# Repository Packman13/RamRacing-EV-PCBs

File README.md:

# RamRacing-EV-PCBs
Full schematic and PCB designs for RAM Racing’s Formula SAE Electric Vehicle. Includes tractive system active light, hard fault latch, precharge/discharge circuits, and the complete EV schematic. Provided for reference and educational purposes.

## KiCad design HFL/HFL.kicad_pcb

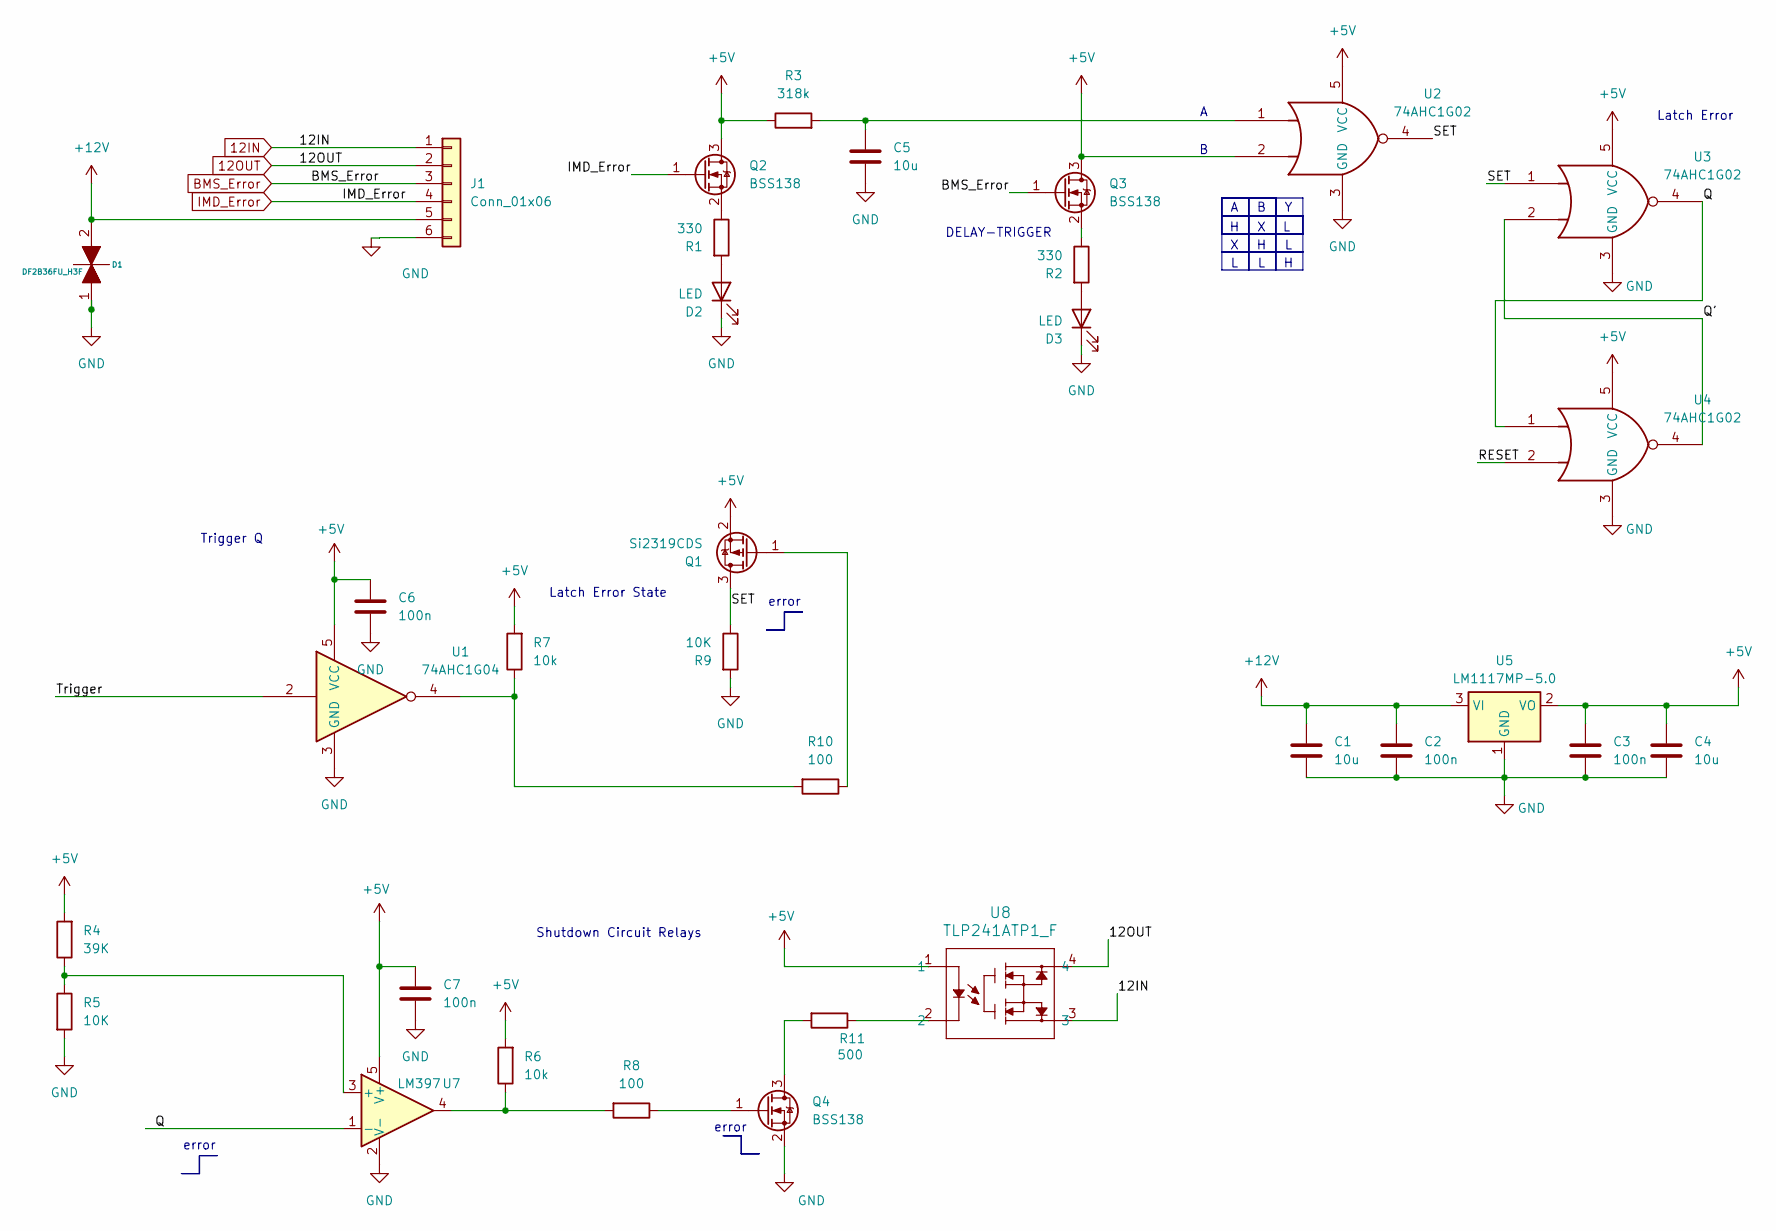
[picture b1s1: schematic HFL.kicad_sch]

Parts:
C1, C4, C5: 10u; C_0603_1608Metric_Pad1.08x0.95mm_HandSolder
C2, C3, C6, C7: 100n; C_0603_1608Metric_Pad1.08x0.95mm_HandSolder
D1: DF2B36FU_H3F; SOD-323 USC_TOS
D2, D3: LED; LED_0805_2012Metric
J1: Conn_01x06; TE_DT13-6P
Q1: Si2319CDS; SOT-23
Q2, Q3, Q4: BSS138; SOT-23
R1, R2: 330; R_0603_1608Metric
R3: 318k; R_0603_1608Metric
R4: 39K; R_0603_1608Metric
R5, R9: 10K; R_0603_1608Metric
R6, R7: 10k; R_0603_1608Metric
R8, R10: 100; R_0603_1608Metric
R11: 500; R_0603_1608Metric
U1: 74AHC1G04; SOT-353_SC-70-5
U2, U3, U4: 74AHC1G02; SOT-353_SC-70-5
U5: LM1117MP-5.0; SOT-223-3_TabPin2
U7: LM397; SOT-23-5
U8: TLP241ATP1_F; D8-L

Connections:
+5V: C3.1, C4.1, C6.1, C7.1, Q1.2 (S), Q2.3 (D), Q3.3 (D), R3.1, R4.2, R6.2, R7.2, U1.5 (VCC), U2.2, U2.5 (VCC), U3.5 (VCC), U4.5 (VCC), U5.2 (VO), U7.5 (V+), U8.1
+12V: C1.1, C2.1, D1.2, J1.5, U5.3 (VI)
/Q: U3.4, U4.1, U7.1 (-)
/Q': U3.2, U4.4
/RESET: U4.2
/SET: Q1.3 (D), R9.1, U2.4, U3.1
/Trigger: U1.2
BMS_Error: J1.3, Q3.1 (G)
GND: C1.2, C2.2, C3.2, C4.2, C5.2, C6.2, C7.2, D1.1, D2.1 (K), D3.1 (K), J1.6, Q4.2 (S), R5.2, R9.2, U1.3 (GND), U2.3 (GND), U3.3 (GND), U4.3 (GND), U5.1 (GND), U7.2 (V-)
IMD_Error: J1.4, Q2.1 (G)
unnamed: C5.1, R3.2, U2.1
unnamed: D2.2 (A), R1.2
unnamed: D3.2 (A), R2.2
unnamed: J1.1, U8.3
unnamed: J1.2, U8.4
unnamed: Q1.1 (G), R10.1
unnamed: Q2.2 (S), R1.1
unnamed: Q3.2 (S), R2.1
unnamed: Q4.3 (D), R11.2
unnamed: Q4.1 (G), R8.1
unnamed: R6.1, R8.2, U7.4
unnamed: R7.1, R10.2, U1.4
unnamed: R11.1, U8.2
unnamed: R4.1, R5.1, U7.3 (+)

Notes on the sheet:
Shutdown Circuit Relays
error
DELAY-TRIGGER
Trigger Q
Latch Error State
Latch Error

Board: 2 copper layers, 30 parts (0 on the bottom side), 17 nets, no tracks yet.

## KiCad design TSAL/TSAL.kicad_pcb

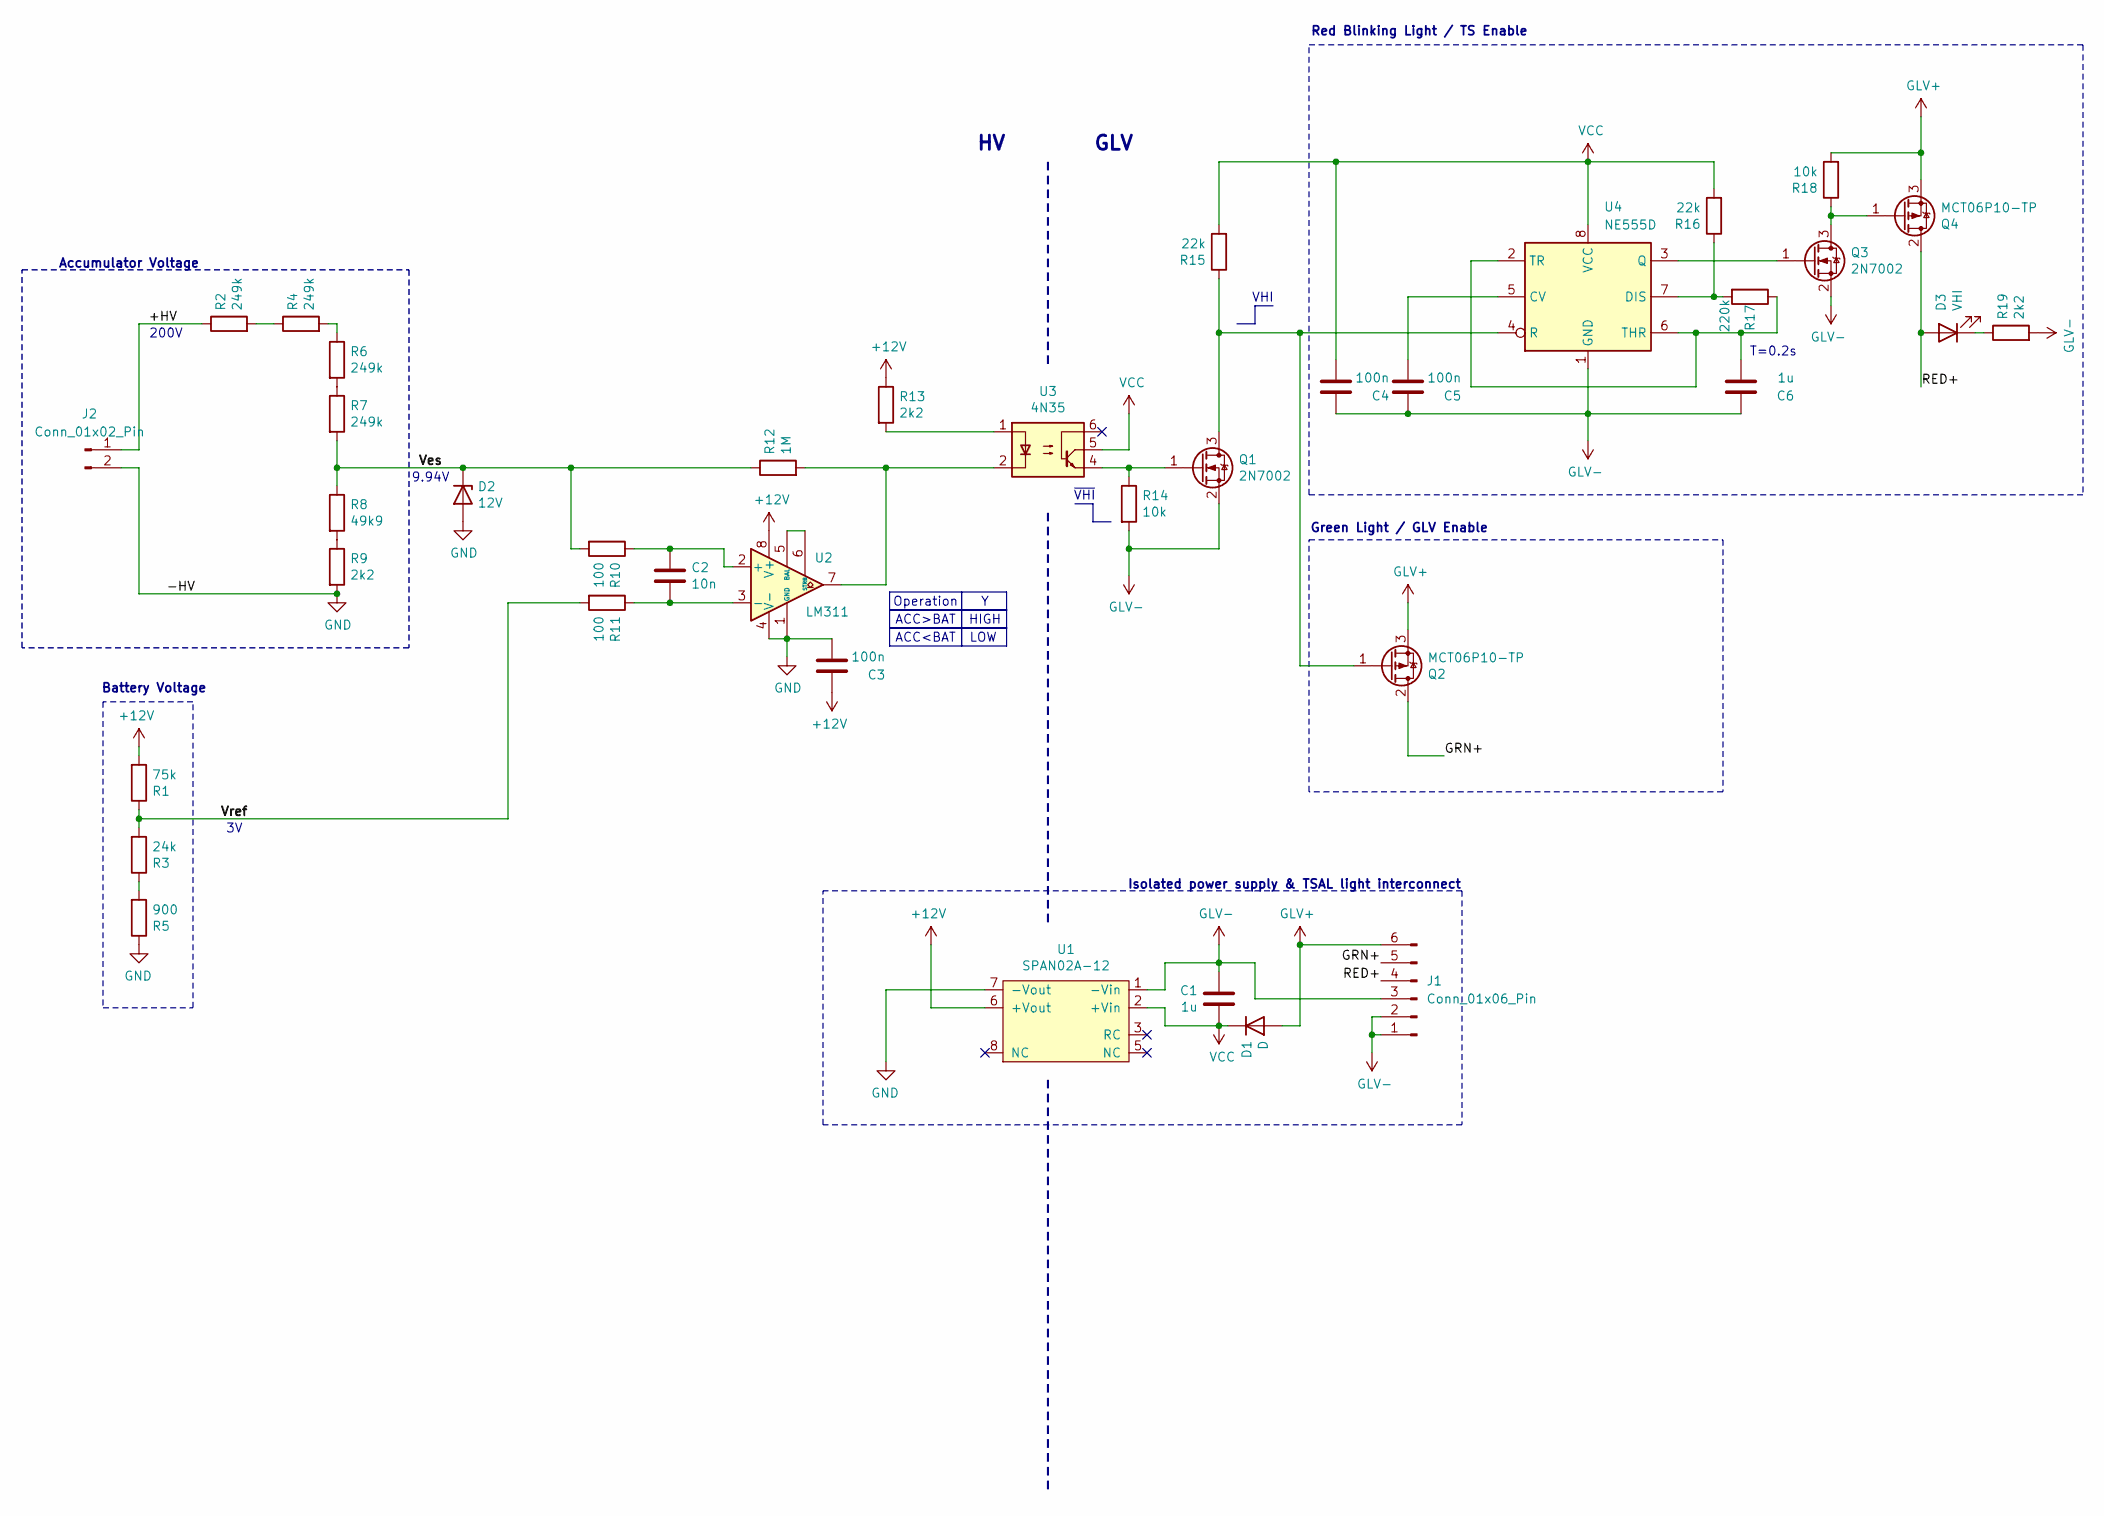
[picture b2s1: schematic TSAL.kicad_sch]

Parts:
C1, C6: 1u; C_0805_2012Metric_Pad1.18x1.45mm_HandSolder
C2: 10n; C_0805_2012Metric_Pad1.18x1.45mm_HandSolder
C3, C4, C5: 100n; C_0805_2012Metric_Pad1.18x1.45mm_HandSolder
D1: D; D_SMA
D2: 12V; D_DO-35_SOD27_P7.62mm_Horizontal
D3: VHI; LED_0805_2012Metric_Pad1.15x1.40mm_HandSolder
J1: Conn_01x06_Pin; Molex_Micro-Fit_3.0_43045-0612_2x03_P3.00mm_Vertical
J2: Conn_01x02_Pin; Molex_Mini-Fit_Jr_5566-02A_2x01_P4.20mm_Vertical
Q1, Q3: 2N7002; SOT-23
Q2, Q4: MCT06P10-TP; SOT-223-3_TabPin2
R1: 75k; R_1206_3216Metric_Pad1.30x1.75mm_HandSolder
R2, R4, R6, R7: 249k; R_1206_3216Metric_Pad1.30x1.75mm_HandSolder
R3: 24k; R_1206_3216Metric_Pad1.30x1.75mm_HandSolder
R5: 900; R_1206_3216Metric_Pad1.30x1.75mm_HandSolder
R8: 49k9; R_1206_3216Metric_Pad1.30x1.75mm_HandSolder
R9, R13, R19: 2k2; R_1206_3216Metric_Pad1.30x1.75mm_HandSolder
R10, R11: 100; R_1206_3216Metric_Pad1.30x1.75mm_HandSolder
R12: 1M; R_1206_3216Metric_Pad1.30x1.75mm_HandSolder
R14, R18: 10k; R_1206_3216Metric_Pad1.30x1.75mm_HandSolder
R15, R16: 22k; R_1206_3216Metric_Pad1.30x1.75mm_HandSolder
R17: 220k; R_1206_3216Metric_Pad1.30x1.75mm_HandSolder
U1: SPAN02A-12; SPAN02
U2: LM311; SOIC-8_3.9x4.9mm_P1.27mm
U3: 4N35; DIP-6_W7.62mm
U4: NE555D; SOIC-8_3.9x4.9mm_P1.27mm

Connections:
+12V: C3.1, R1.2, R13.1, U1.6 (+Vout), U2.8 (V+)
/+HV: J2.1, R2.1
/GRN+: J1.5, Q2.2 (D)
/RED+: D3.2 (A), J1.4, Q4.2 (D)
/Ves: D2.1 (K), R7.2, R8.1, R10.2, R12.1
/Vref: R1.1, R3.2, R11.2
GLV+: D1.2 (A), J1.6, Q2.3 (S), Q4.3 (S), R18.2
GLV-: C1.1, C4.1, C5.1, C6.1, J1.1, J1.2, J1.3, Q1.2 (S), Q3.2 (S), R14.2, R19.2, U1.1 (-Vin), U4.1 (GND)
GND: C3.2, D2.2 (A), J2.2, R5.1, R9.2, U1.7 (-Vout), U2.1 (GND), U2.4 (V-)
unnamed: D3.1 (K), R19.1
unnamed: Q1.3 (D), Q2.1 (G), R15.1, U4.4 (R)
unnamed: Q1.1 (G), R14.1, U3.4
unnamed: Q3.3 (D), Q4.1 (G), R18.1
unnamed: Q3.1 (G), U4.3 (Q)
unnamed: R2.2, R4.1
unnamed: R3.1, R5.2
unnamed: R4.2, R6.1
unnamed: R6.2, R7.1
unnamed: R8.2, R9.1
unnamed: R12.2, U2.7, U3.2
unnamed: R13.2, U3.1
unnamed: C2.1, R10.1, U2.2 (+)
unnamed: C2.2, R11.1, U2.3 (-)
unnamed: U2.5 (BAL), U2.6 (STRB)
unnamed: C5.2, U4.5 (CV)
unnamed: R16.1, R17.2, U4.7 (DIS)
unnamed: C6.2, R17.1, U4.2 (TR), U4.6 (THR)
VCC: C1.2, C4.2, D1.1 (K), R15.2, R16.2, U1.2 (+Vin), U3.5, U4.8 (VCC)

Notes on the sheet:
Accumulator Voltage
Green Light / GLV Enable
T=0.2s
Battery Voltage
ACC<BAT
Isolated power supply & TSAL light interconnect
VHI
Operation
LOW
200V
ACC>BAT
Red Blinking Light / TS Enable
9.94V
~{VHI}
GLV
HIGH

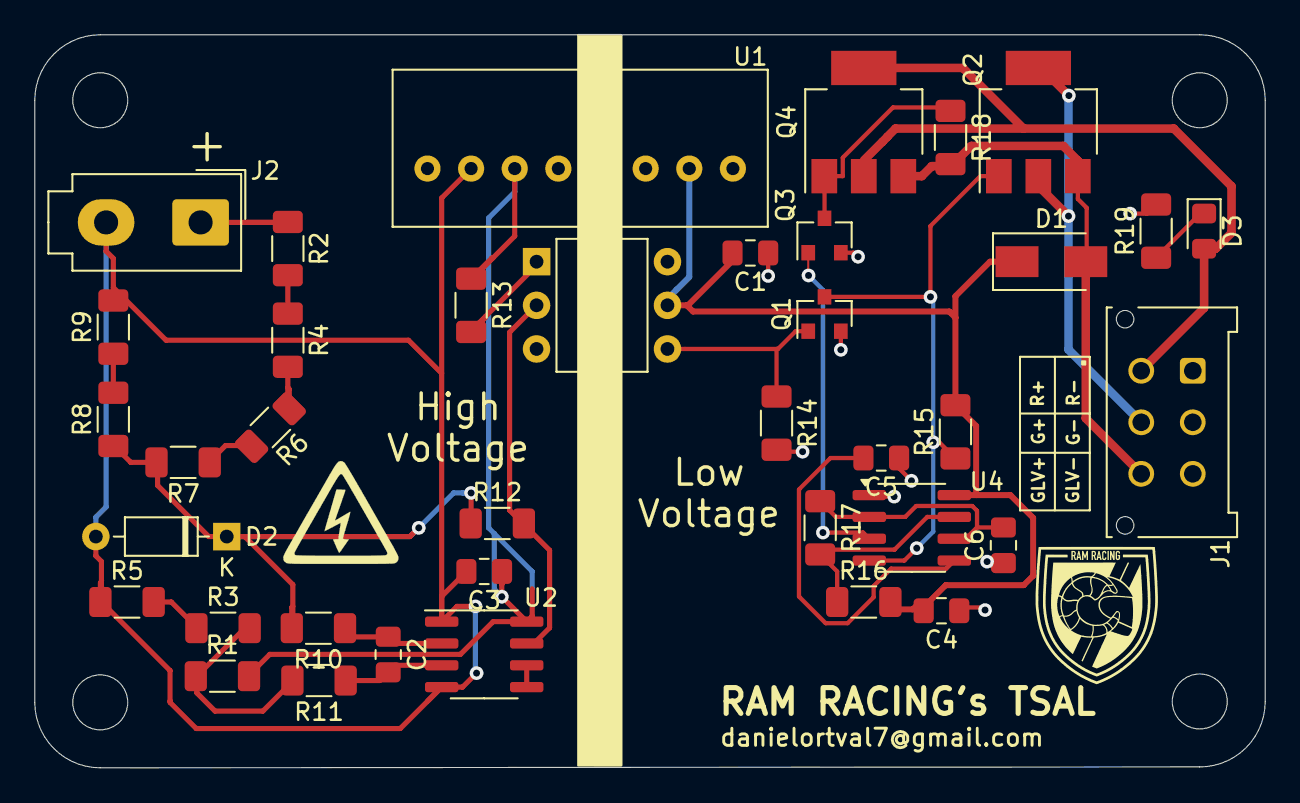
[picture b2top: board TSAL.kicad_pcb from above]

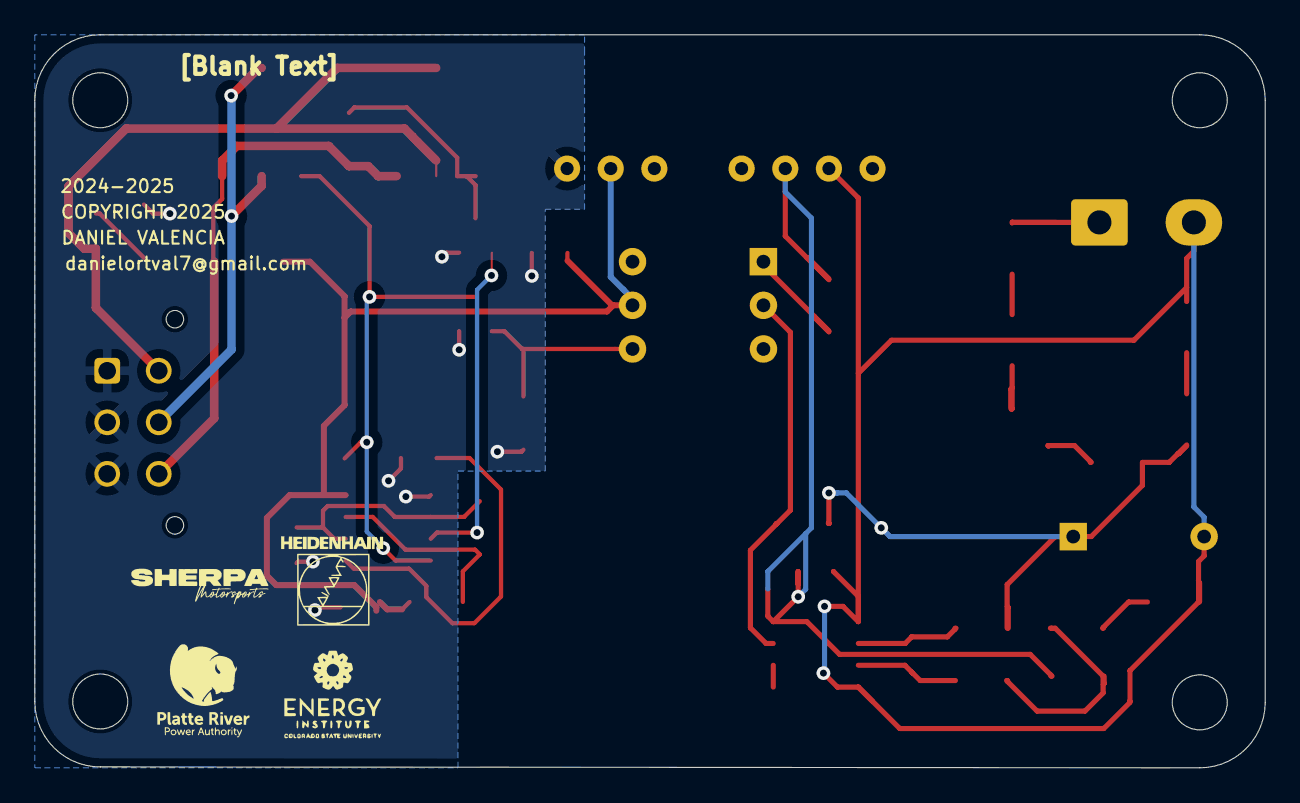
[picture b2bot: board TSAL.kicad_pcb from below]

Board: 2 copper layers, 71.6 x 42.7 mm, 47 parts (3 on the bottom side), 28 nets.

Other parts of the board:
G2: LOGO; electric-shock-symbol
H1: LOGO; Sherpalogo
H2: LOGO; HHlogo
H3: LOGO; EIlogo
H5: LOGO; RRlogo
MH1, MH2, MH3, MH4: MountingHole_3.2mm_M3

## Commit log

2025-09-14 Initial commit: Full EV schematics
    Includes complete schematic of the Formula SAE Electric Vehicle:
    - Motor controller and motor peripherals
    - Fuse box and protection circuits
    - Dashboard and driver interface
    - Precharge/discharge circuits
    - Hard fault latch and tractive system active light
2025-09-14 Add Tractive System Active Light (TSAL) schematic
    Includes complete schematic for the Tractive System Active Light (TSAL):
    - High-voltage sensing and safety indication
    - LED driver and visibility requirements per FSAE rules
    - Integration with accumulator and shutdown circuit
    - Connection details to dashboard and wiring harness
2025-09-14 Add Hard Fault Latch (HFL)
    Includes complete schematic for the Hard Fault Latch (HFL):
    - Fault detection and latching circuit
    - Interfaces with IMD, BMS, and other shutdown sources
    - Provides persistent shutdown signal until system reset
    - Integrated into the Tractive System Master Switch (TSMS) and shutdown circuit

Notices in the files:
TSAL/TSAL.kicad_pcb:
COPYRIGHT 2025
